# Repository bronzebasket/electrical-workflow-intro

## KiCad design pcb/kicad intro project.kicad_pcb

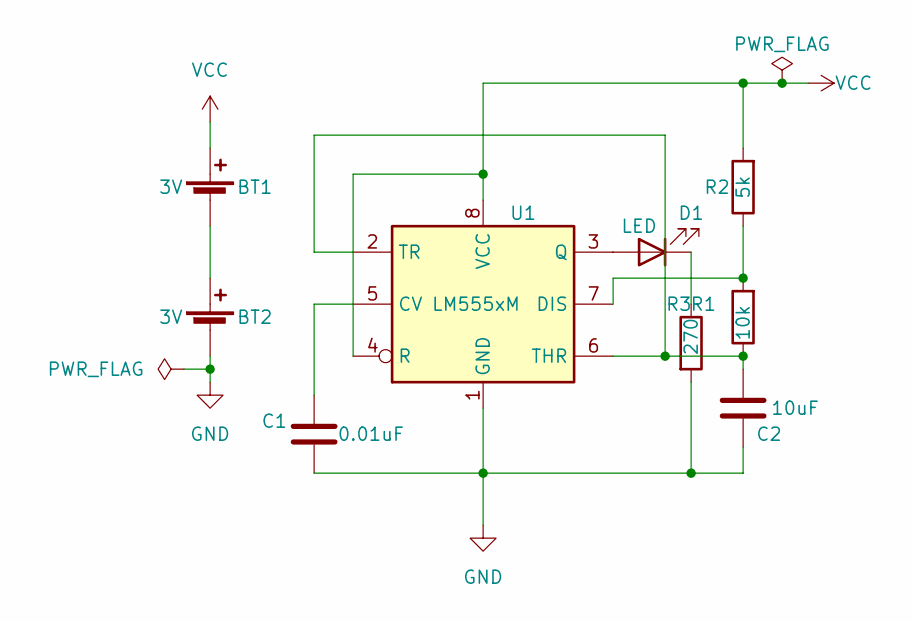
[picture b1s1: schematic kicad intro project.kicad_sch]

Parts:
BT1, BT2: 3V; BatteryHolder_LINX_BAT-HLD-012-SMT
C1: 0.01uF; C_0805_2012Metric_Pad1.18x1.45mm_HandSolder
C2: 10uF; C_0805_2012Metric_Pad1.18x1.45mm_HandSolder
D1: LED; LED_0805_2012Metric_Pad1.15x1.40mm_HandSolder
R1: 10k; R_0805_2012Metric_Pad1.20x1.40mm_HandSolder
R2: 5k; R_0805_2012Metric_Pad1.20x1.40mm_HandSolder
R3: 270; R_0805_2012Metric_Pad1.20x1.40mm_HandSolder
U1: LM555xM; SOIC-8_3.9x4.9mm_P1.27mm

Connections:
GND: BT2.2 (-), C1.1, C2.1, R3.2, U1.1 (GND)
unnamed: BT1.2 (-), BT2.1 (+)
unnamed: C1.2, U1.5 (CV)
unnamed: C2.2, R1.1, U1.2 (TR), U1.6 (THR)
unnamed: D1.1 (K), R3.1
unnamed: D1.2 (A), U1.3 (Q)
unnamed: R1.2, R2.1, U1.7 (DIS)
VCC: BT1.1 (+), R2.2, U1.4 (R), U1.8 (VCC)

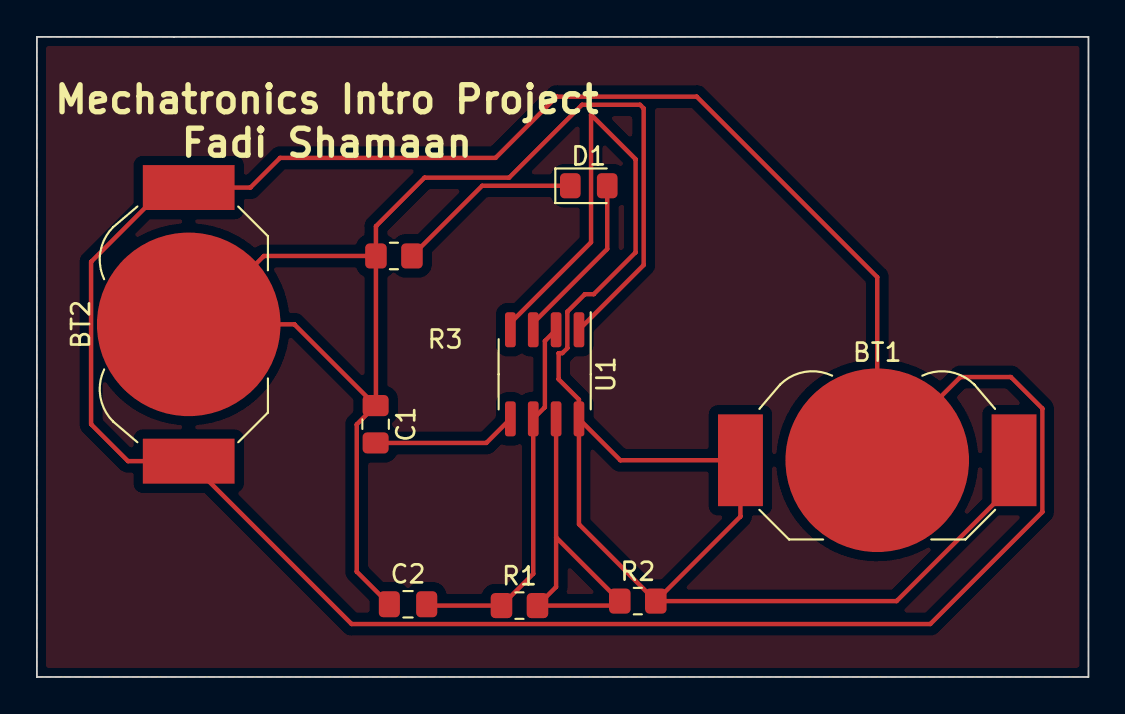
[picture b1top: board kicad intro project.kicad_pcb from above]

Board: 2 copper layers, 58.4 x 35.6 mm, 9 parts (0 on the bottom side), 8 nets.

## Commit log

2022-01-29 Hello, my name is Fadi Shamaan. I am an Electrical Engineering student at SDSU. My goal for this semester is to figure out exactly what to specialize in as an electrical engineer
2022-01-29 git commit -m
2022-01-29 Hello everyone, my name is Fadi Shamaan. I am a third year electrical engineering student. My goal this semester is to figure out what I want to specialize in as an electrical engineer
2022-01-29 Hello everyone, my name is Fadi Shamaan. I am a third year electrical engineering student. My goal this semester is to figure out what I want to specialize in as an electrical engineer.
2022-01-29 Hello everyone, my name is Fadi. I am a third year electrical engineering student. My goal for this semester is to figure out what I want to specialize in as an electrical engineer.
2022-01-29 changed files in Fadi_dev
2022-01-29 add intro
2022-01-29 add intro. Edit: Spelling
2022-02-14 added all pcb files
2022-02-20 added standalone pcb gerber files zip
2022-03-22 Create Introduction
